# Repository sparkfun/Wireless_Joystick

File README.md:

SparkFun Wireless Joystick Kit
=============================================

[*SparkFun Wireless Joystick Kit (KIT-14051)*](https://www.sparkfun.com/products/14051)

What's in the kit:

* 1 - Wireless Joystick Board
* 2 - [Thumb Joysticks](https://www.sparkfun.com/products/9032)
* 2 - [Right Angle Momentary Push-Buttons](https://www.sparkfun.com/products/10791)
* 4 - [12mm Square Momentary Push Buttons](https://www.sparkfun.com/products/9190)

What's **not** in the kit:

* 1 - [Li-Ion battery](https://www.sparkfun.com/products/13851)
* 1 - [XBee](https://www.sparkfun.com/products/8665)

The SparkFun Wireless Joystick Kit is a customizable XBee wireless controller with a SAMD21 at the heart of the board. The controller can be configured in two ways; gamepad or dual-stick. The gamepad has a layout similar to the SNES gamepad, with a single joystick on the left and four push-buttons on the right, and two trigger buttons. The dual-stick configuration uses two analog joysticks, along with two trigger buttons. Dual joysticks are perfect for tank-steering robotics; the left joystick controls the motor(s) on the left side, and the right  joystick controls the motor(s) on the right side.
 
 Repository Contents
-------------------
* **/Hardware** - All Eagle design files (.brd, .sch)

Documentation
-------------------
* [**Hookup Guide**](https://learn.sparkfun.com/tutorials/wireless-joystick-hookup-guide)

License Information
-------------------
The hardware is released under [Creative Commons ShareAlike 4.0 International](https://creativecommons.org/licenses/by-sa/4.0/).
The code is beerware; if you see me (or any other SparkFun employee) at the local, and you've found our code helpful, please buy us a round!

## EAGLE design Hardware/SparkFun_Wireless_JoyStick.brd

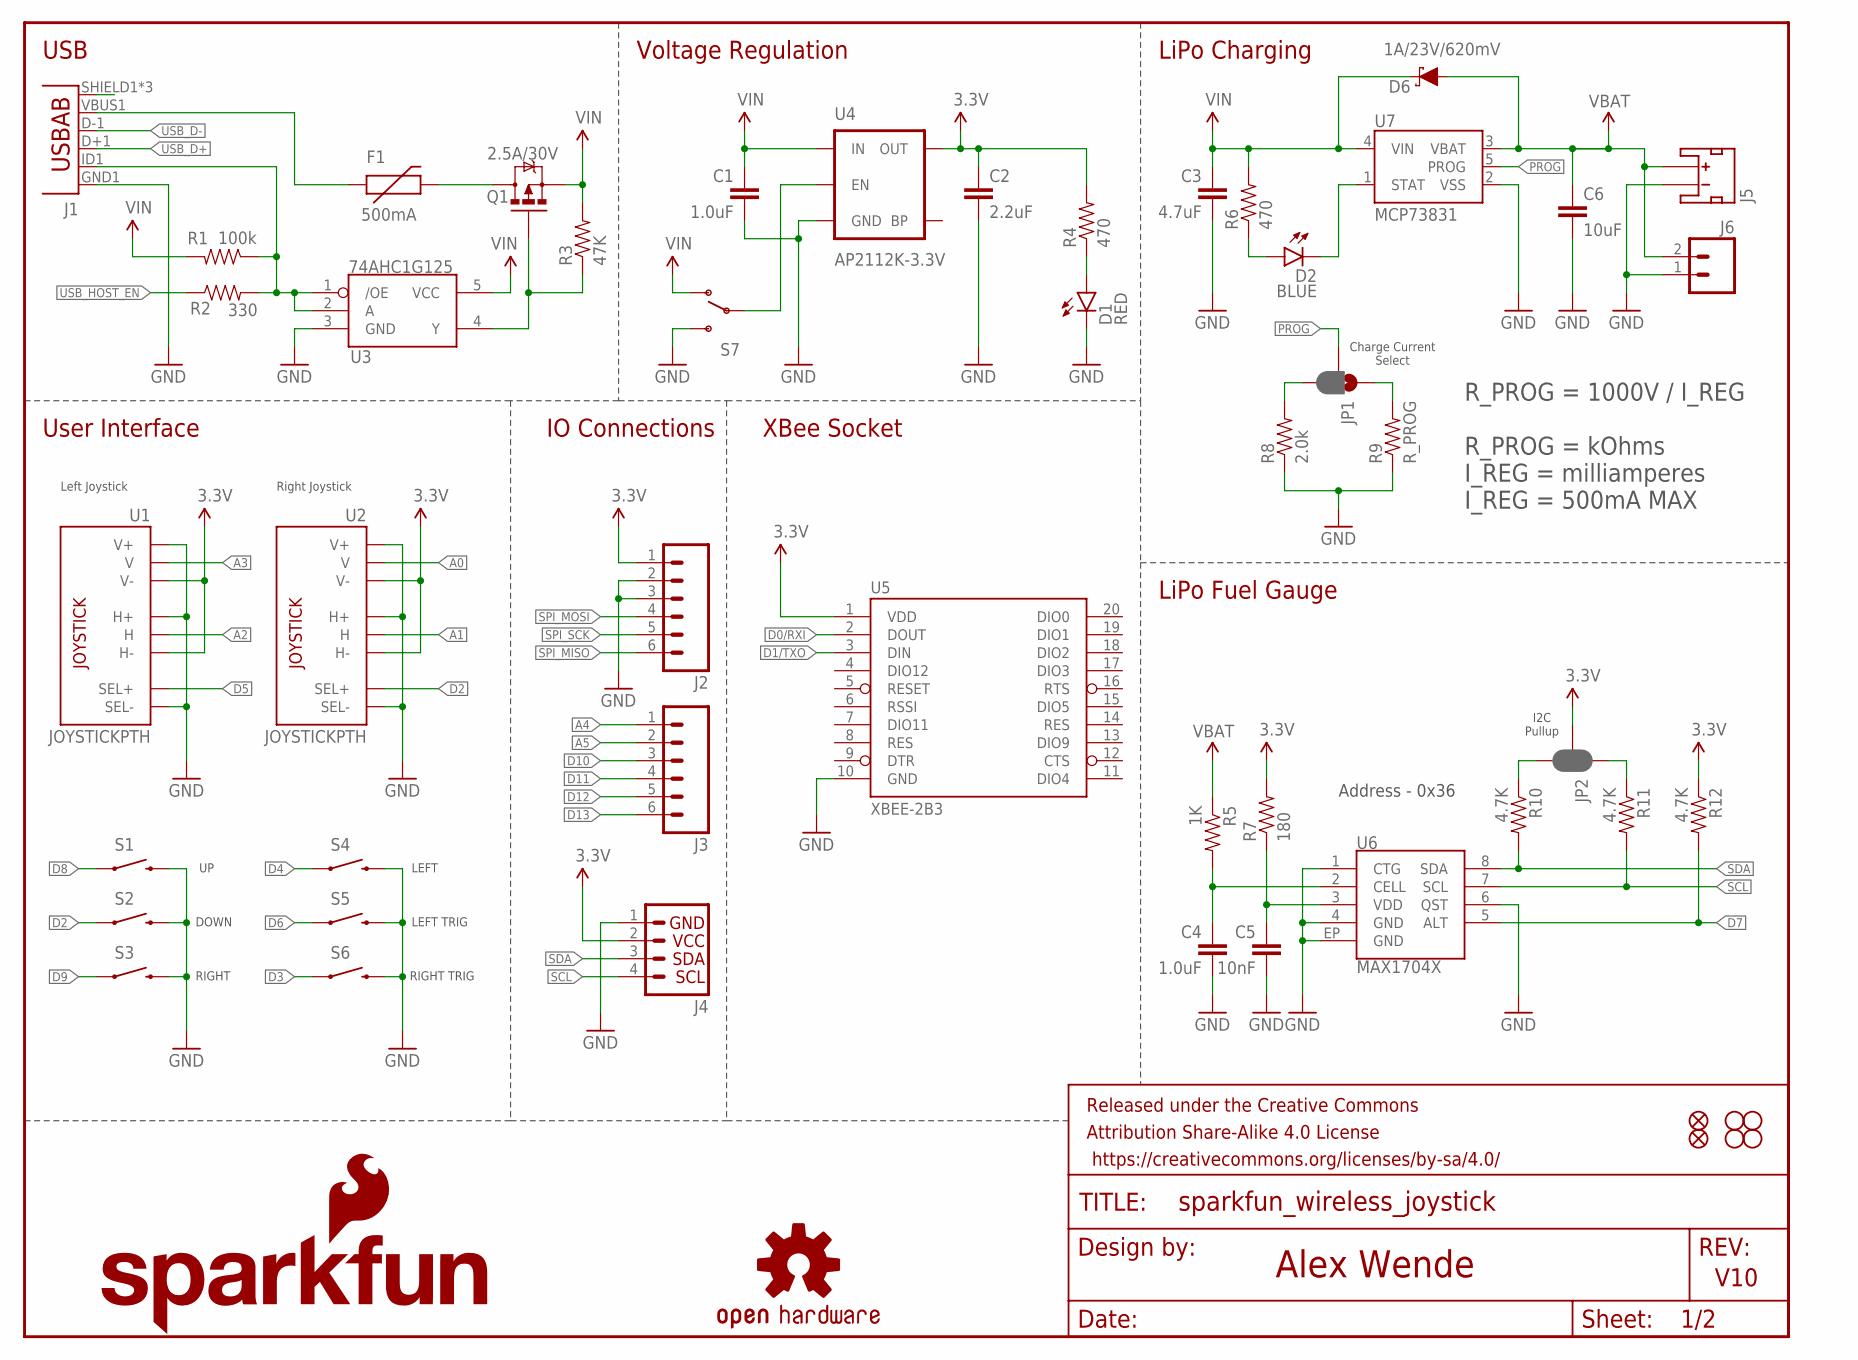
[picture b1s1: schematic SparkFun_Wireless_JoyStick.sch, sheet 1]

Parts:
C1: 1.0uF; 0805-CAP
C2: 2.2uF; 0603-CAP
C3: 4.7uF; 0603-CAP
C4: 1.0uF; 0603-CAP
C5: 10nF; 0603-CAP
C6: 10uF; 0603-CAP
D1: RED; LED-0603
D2: BLUE; LED-0603
D6: 1A/23V/620mV; SOD-323
F1: 500mA; PTC-1206
FD1, FD2: FIDUCIALUFIDUCIAL; MICRO-FIDUCIAL
FRAME1: FRAME-LETTER; CREATIVE_COMMONS
H1, H2, H3, H4: STAND-OFF
J1: USB-ABCONN-11794; USB-AB-MICRO-SMD_V03
J2, J3: M06NO_SILK_FEMALE_PTH; 1X06_NO_SILK
J4: I2C_STANDARD_NO_SILK; 1X04_NO_SILK
J5: JST_2MM_MALE; JST-2-SMD
J6: M021X02_NO_SILK; 1X02_NO_SILK
JP1: JUMPER-PAD-3-2OF3_NC_BY_PASTE; PAD-JUMPER-3-2OF3_NC_BY_PASTE_YES_SILK_FULL_BOX
JP2: JUMPER-PAD-3-NC_BY_PASTE; PAD-JUMPER-3-NC_BY_PASTE_YES_SILK_FULL_BOX
LOGO1: SFE_LOGO_NAME_FLAME.3_INCH; SFE_LOGO_NAME_FLAME_.3
LOGO2: OSHW-LOGOL; OSHW-LOGO-L
Q1: 2.5A/30V; SOT23-3@1
R1: 100k; 0603-RES
R2: 330; 0603-RES
R3: 47K; 0603-RES
R4, R6: 470; 0603-RES
R5: 1K; 0603-RES
R7: 180; 0603-RES
R8: 2.0k; 0603-RES
R9: R_PROG; AXIAL-0.4
R10, R11, R12: 4.7K; 0603-RES
S1, S2, S3, S4: SWITCH-MOMENTARY-212MM; TACTILE-PTH-12MM
S5, S6: SWITCH-MOMENTARY-2SIDE_EZ; TACTILE-PTH-SIDEEZ
S7: SWITCH_SPDT; KPS-1290
U1, U2: JOYSTICKPTH; JOYSTICK
U3: 74AHC1G125; SOT23-5
U4: AP2112K-3.3V; SOT23-5
U5: XBEE-2B3; XBEE-SMD
U6: MAX1704X; TDFN-8
U7: MCP73831; SOT23-5

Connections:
3.3V: C2.1, J2.1, J4.2, JP2.2, R4.2, R7.2, R12.1, U1.H3 (H-), U1.V3 (V-), U2.H3 (H-), U2.V3 (V-), U4.5 (OUT), U5.1 (VDD); also elsewhere on the board
A0: U2.V2 (V); also elsewhere on the board
A1: U2.H2 (H); also elsewhere on the board
A2: U1.H2 (H); also elsewhere on the board
A3: U1.V2 (V); also elsewhere on the board
A4: J3.1; also elsewhere on the board
A5: J3.2; also elsewhere on the board
D0/RXI: U5.2 (DOUT); also elsewhere on the board
D1/TXO: U5.3 (DIN); also elsewhere on the board
D2: S2.1, U2.B1A (SEL+); also elsewhere on the board
D3: S6.1; also elsewhere on the board
D4: S4.1; also elsewhere on the board
D5: U1.B1A (SEL+); also elsewhere on the board
D6: S5.1; also elsewhere on the board
D7: R12.2, U6.5 (ALT); also elsewhere on the board
D8: S1.1; also elsewhere on the board
D9: S3.1; also elsewhere on the board
D10: J3.3; also elsewhere on the board
D11: J3.4; also elsewhere on the board
D12: J3.5; also elsewhere on the board
D13: J3.6; also elsewhere on the board
GND: C1.2, C2.2, C3.2, C4.2, C5.2, C6.2, D1.C, J1.GND1 (GND), J2.2, J2.3, J4.1, J5.1 (-), J6.1, R8.1, R9.P$1 (1), S1.3 (2), S2.3 (2), S3.3 (2), S4.3 (2), S5.2, S6.2, S7.S, U1.B2A (SEL-), U1.H1 (H+), U1.V1 (V+), U2.B2A (SEL-), U2.H1 (H+), U2.V1 (V+), U3.3 (GND), U4.2 (GND), U5.10 (GND), U6.1 (CTG), U6.4 (GND), U6.6 (QST), U6.EP (GND), U7.2 (VSS); also elsewhere on the board
unnamed: JP2.1, R11.1
unnamed: JP2.3, R10.1
unnamed: JP1.1, R9.P$2 (2)
unnamed: F1.1, J1.VBUS1 (VBUS)
unnamed: C5.1, R7.1, U6.3 (VDD)
unnamed: S7.P, U4.3 (EN)
unnamed: F1.2, Q1.3 (D)
unnamed: J1.ID1 (USBID), R1.1, R2.2, U3.1 (/OE), U3.2 (A)
unnamed: C4.1, R5.2, U6.2 (CELL)
unnamed: JP1.3, R8.2
unnamed: D2.A, R6.1
unnamed: D2.C, U7.1 (STAT)
unnamed: D1.A, R4.1
unnamed: Q1.1 (G), R3.1, U3.4 (Y)
PROG: JP1.2, U7.5 (PROG)
SCL: J4.4, R11.2, U6.7 (SCL); also elsewhere on the board
SDA: J4.3, R10.2, U6.8 (SDA); also elsewhere on the board
SHIELD: J1.SHIELD1 (SHIELD), J1.SHIELD2 (SHIELD), J1.SHIELD3 (SHIELD)
SPI_MISO: J2.6; also elsewhere on the board
SPI_MOSI: J2.4; also elsewhere on the board
SPI_SCK: J2.5; also elsewhere on the board
USB_D+: J1.D+1 (D+); also elsewhere on the board
USB_D-: J1.D-1 (D-); also elsewhere on the board
USB_HOST_EN: R2.1; also elsewhere on the board
VBAT: C6.1, D6.A, J5.2 (+), J6.2, R5.1, U7.3 (VBAT)
VIN: C1.1, C3.1, D6.C, Q1.2 (S), R1.2, R3.2, R6.2, S7.O, U3.5 (VCC), U4.1 (IN), U7.4 (VIN)

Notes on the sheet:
User Interface
USB
LiPo Charging
Voltage Regulation
XBee Socket
R_PROG = 1000V / I_REG
R_PROG = kOhms I_REG = milliamperes I_REG = 500mA MAX
LiPo Fuel Gauge
Alex Wende
V10
Right Joystick
Left Joystick
DOWN
RIGHT
LEFT
LEFT TRIG
RIGHT TRIG
IO Connections
I2C Pullup
Charge Current Select
Address - 0x36

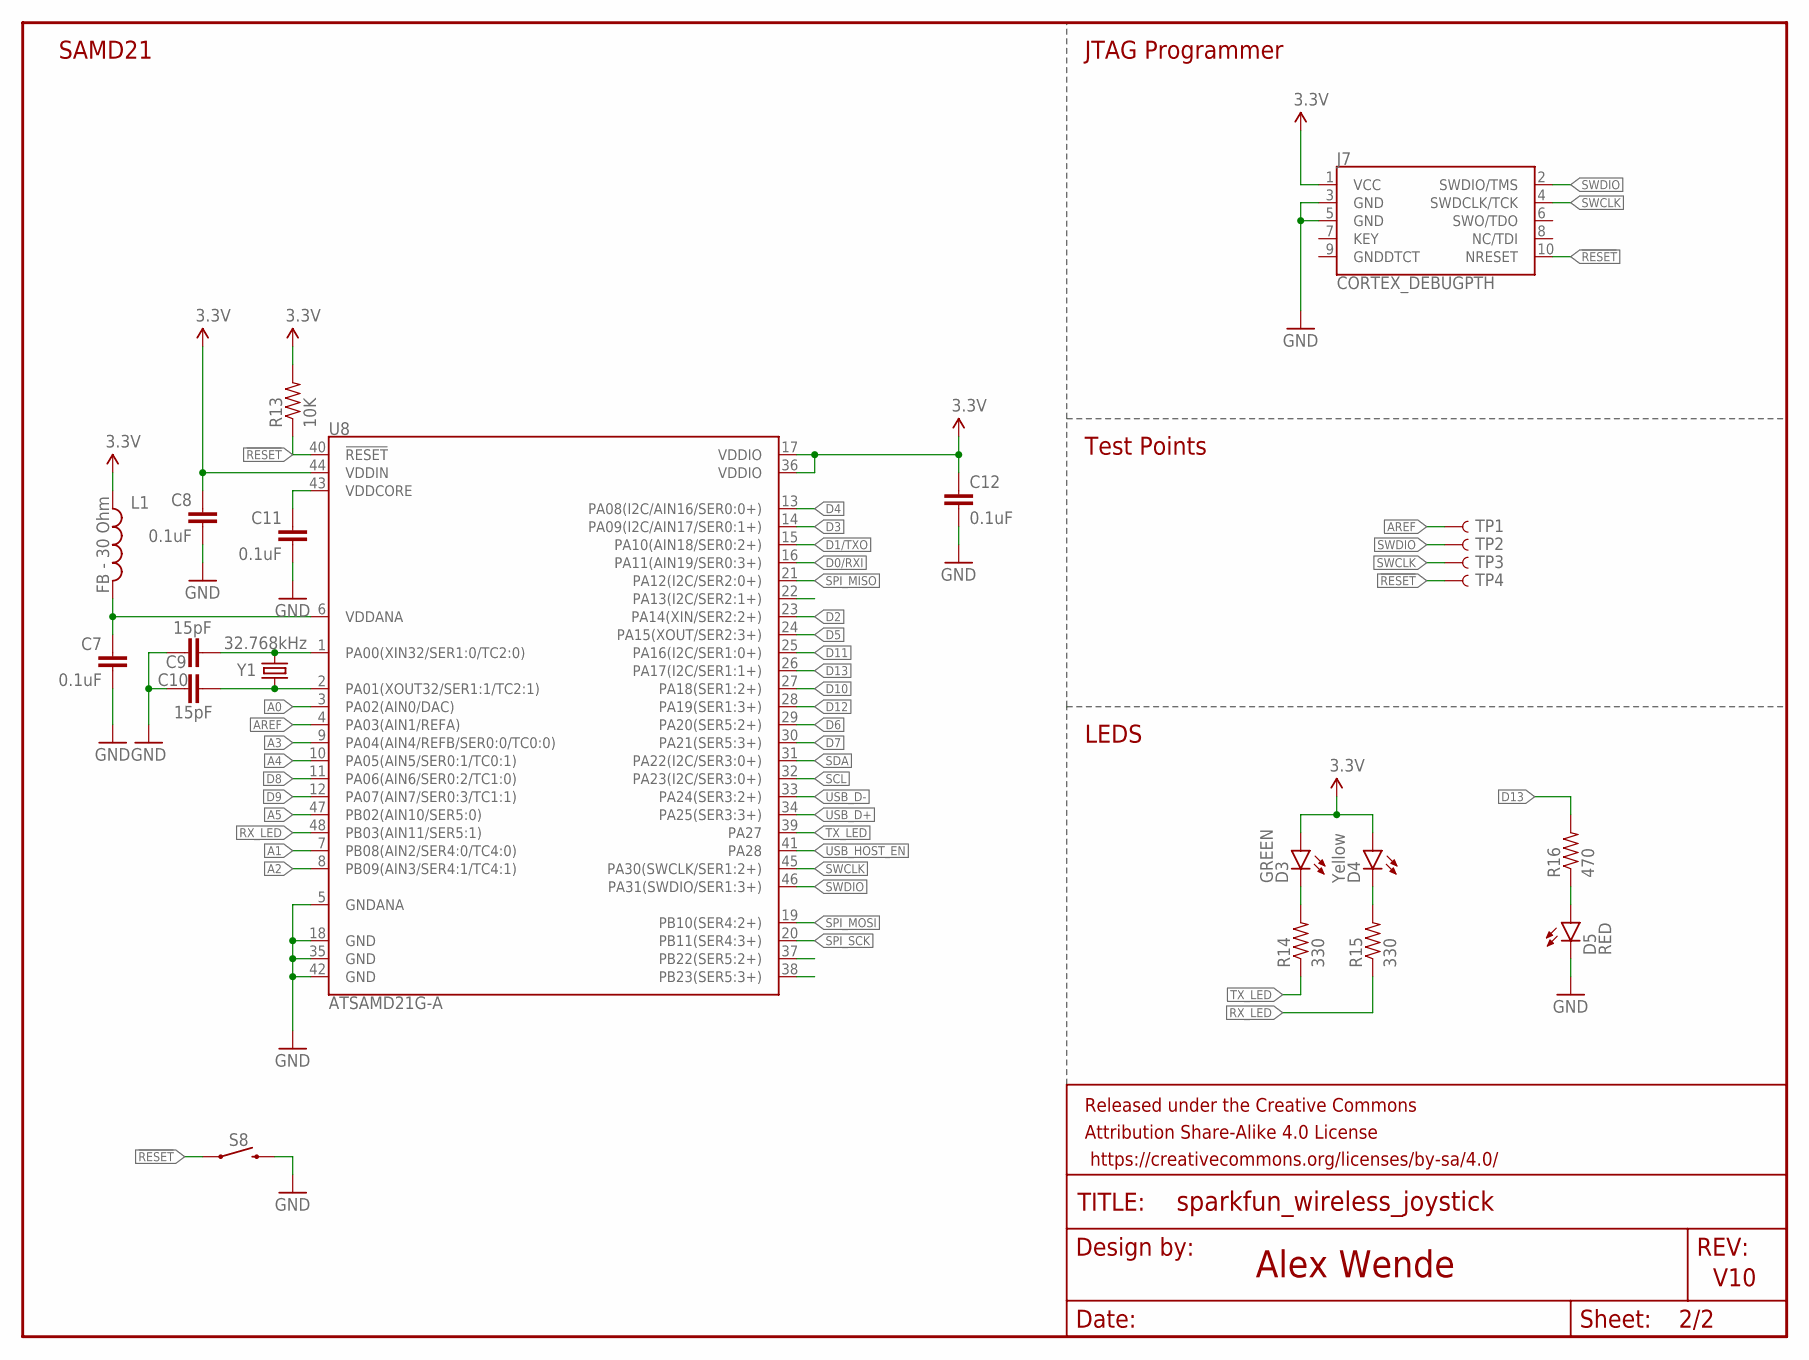
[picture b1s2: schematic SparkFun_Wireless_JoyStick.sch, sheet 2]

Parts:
C7, C8, C11, C12: 0.1uF; 0603-CAP
C9, C10: 15pF; 0603-CAP
D3: GREEN; LED-0603
D4: Yellow; LED-0603
D5: RED; LED-0603
FRAME2: FRAME-LETTERNO_PACKAGE; DUMMY
J7: CORTEX_DEBUGPTH; 2X5-PTH-1.27MM
L1: FB - 30 Ohm; 0603
R13: 10K; 0603-RES
R14, R15: 330; 0603-RES
R16: 470; 0603-RES
S8: MOMENTARY-SWITCH-SPST-SMD-4.6X2.8MM; TACTILE_SWITCH_SMD_4.6X2.8MM
TP1, TP2, TP3, TP4: TEST-POINT3; PAD.03X.03
U8: ATSAMD21G-A; TQFP-48
Y1: 32.768kHz; CRYSTAL-SMD-3.2X1.5MM

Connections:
3.3V: C8.1, C12.1, D3.A, D4.A, J7.1 (VCC), L1.1, R13.2, U8.17 (VDDIO), U8.36 (VDDIO), U8.44 (VDDIN); also elsewhere on the board
!RESET: J7.10 (NRESET), R13.1, S8.1, S8.2 (1), TP4.P$1, U8.40 (!RESET!)
A0: U8.3 (PA02(AIN0/DAC)); also elsewhere on the board
A1: U8.7 (PB08(AIN2/SER4:0/TC4:0)); also elsewhere on the board
A2: U8.8 (PB09(AIN3/SER4:1/TC4:1)); also elsewhere on the board
A3: U8.9 (PA04(AIN4/REFB/SER0:0/TC0:0)); also elsewhere on the board
A4: U8.10 (PA05(AIN5/SER0:1/TC0:1)); also elsewhere on the board
A5: U8.47 (PB02(AIN10/SER5:0)); also elsewhere on the board
AREF: TP1.P$1, U8.4 (PA03(AIN1/REFA))
D0/RXI: U8.16 (PA11(AIN19/SER0:3+)); also elsewhere on the board
D1/TXO: U8.15 (PA10(AIN18/SER0:2+)); also elsewhere on the board
D2: U8.23 (PA14(XIN/SER2:2+)); also elsewhere on the board
D3: U8.14 (PA09(I2C/AIN17/SER0:1+)); also elsewhere on the board
D4: U8.13 (PA08(I2C/AIN16/SER0:0+)); also elsewhere on the board
D5: U8.24 (PA15(XOUT/SER2:3+)); also elsewhere on the board
D6: U8.29 (PA20(SER5:2+)); also elsewhere on the board
D7: U8.30 (PA21(SER5:3+)); also elsewhere on the board
D8: U8.11 (PA06(AIN6/SER0:2/TC1:0)); also elsewhere on the board
D9: U8.12 (PA07(AIN7/SER0:3/TC1:1)); also elsewhere on the board
D10: U8.27 (PA18(SER1:2+)); also elsewhere on the board
D11: U8.25 (PA16(I2C/SER1:0+)); also elsewhere on the board
D12: U8.28 (PA19(SER1:3+)); also elsewhere on the board
D13: R16.2, U8.26 (PA17(I2C/SER1:1+)); also elsewhere on the board
GND: C7.2, C8.2, C9.1, C10.1, C11.2, C12.2, D5.C, J7.3 (GND), J7.5 (GND), S8.3 (2), S8.4 (2), U8.5 (GNDANA), U8.18 (GND), U8.35 (GND), U8.42 (GND); also elsewhere on the board
unnamed: D4.C, R15.2
unnamed: D5.A, R16.1
unnamed: D3.C, R14.2
unnamed: C11.1, U8.43 (VDDCORE)
unnamed: C9.2, U8.1 (PA00(XIN32/SER1:0/TC2:0)), Y1.P$2 (2)
unnamed: C10.2, U8.2 (PA01(XOUT32/SER1:1/TC2:1)), Y1.P$1 (1)
unnamed: C7.1, L1.2, U8.6 (VDDANA)
RX_LED: R15.1, U8.48 (PB03(AIN11/SER5:1))
SCL: U8.32 (PA23(I2C/SER3:0+)); also elsewhere on the board
SDA: U8.31 (PA22(I2C/SER3:0+)); also elsewhere on the board
SPI_MISO: U8.21 (PA12(I2C/SER2:0+)); also elsewhere on the board
SPI_MOSI: U8.19 (PB10(SER4:2+)); also elsewhere on the board
SPI_SCK: U8.20 (PB11(SER4:3+)); also elsewhere on the board
SWCLK: J7.4 (SWDCLK/TCK), TP3.P$1, U8.45 (PA30(SWCLK/SER1:2+))
SWDIO: J7.2 (SWDIO/TMS), TP2.P$1, U8.46 (PA31(SWDIO/SER1:3+))
TX_LED: R14.1, U8.39 (PA27)
USB_D+: U8.34 (PA25(SER3:3+)); also elsewhere on the board
USB_D-: U8.33 (PA24(SER3:2+)); also elsewhere on the board
USB_HOST_EN: U8.41 (PA28); also elsewhere on the board

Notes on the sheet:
Alex Wende
V10
SAMD21
JTAG Programmer
Test Points
LEDS

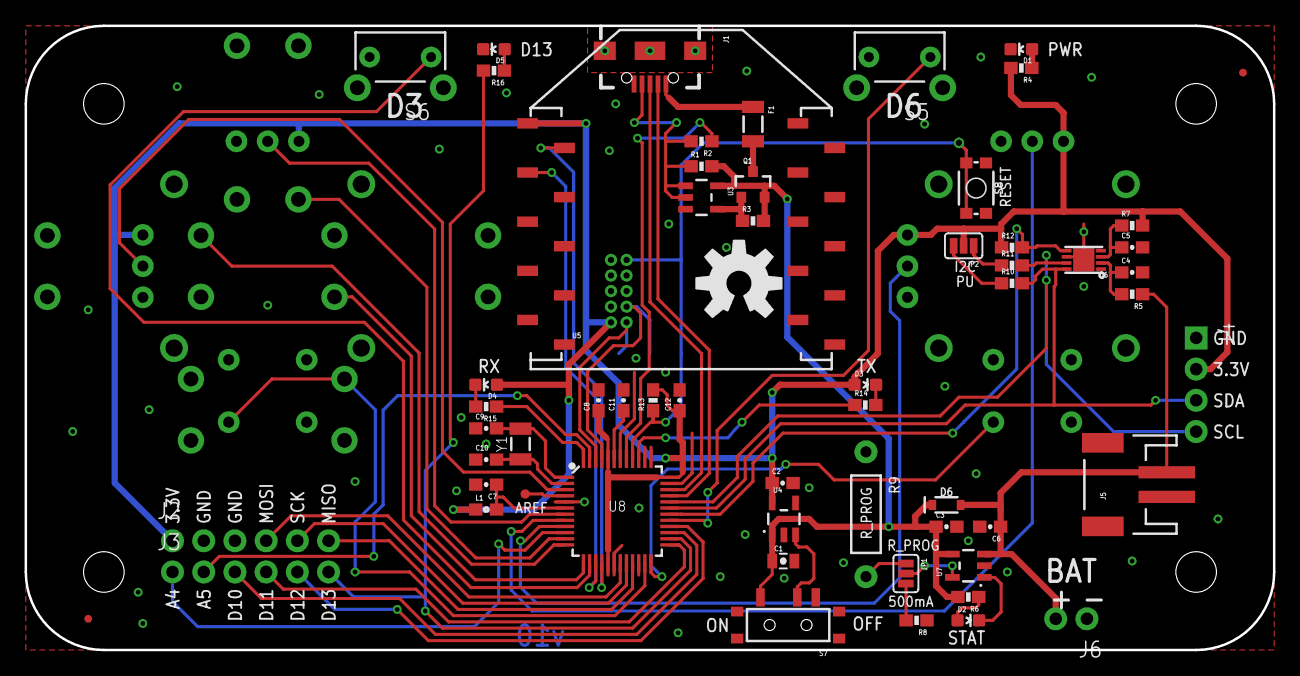
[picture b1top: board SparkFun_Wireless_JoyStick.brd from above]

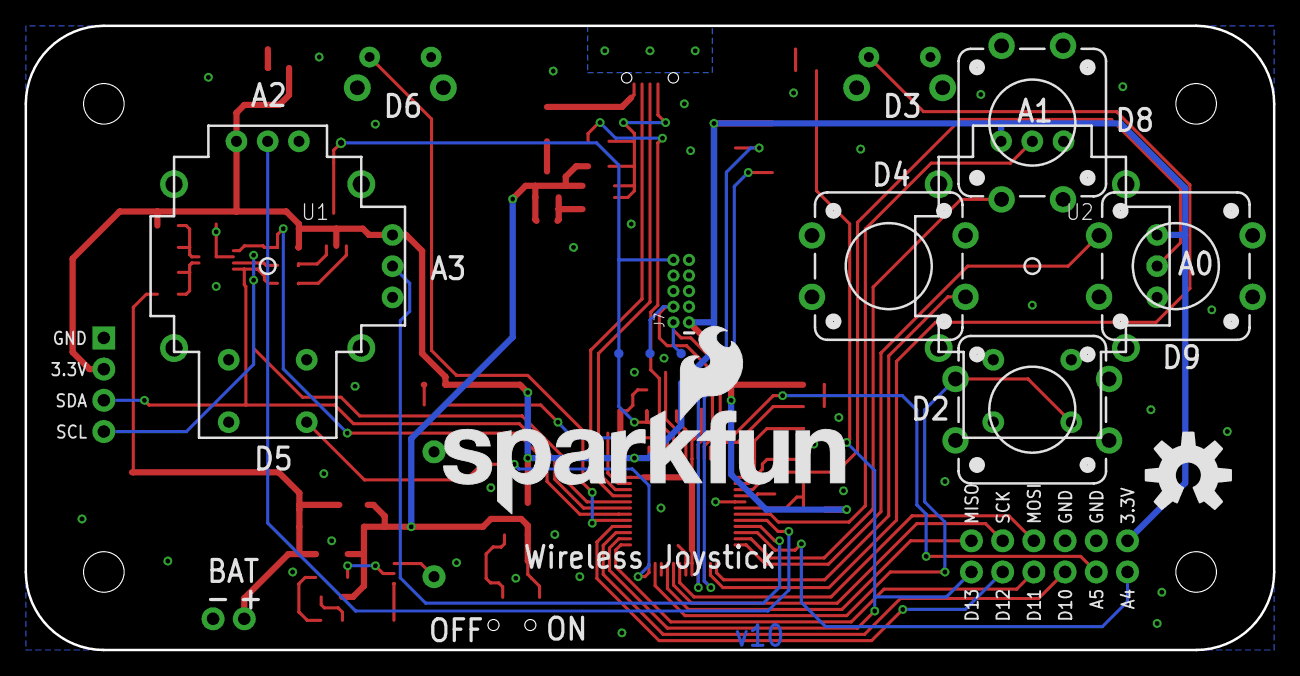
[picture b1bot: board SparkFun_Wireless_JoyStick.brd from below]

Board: 2 copper layers, 101.6 x 50.8 mm, 78 parts (12 on the bottom side), 61 nets.

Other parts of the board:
LOGO3: OSHW-LOGOL; OSHW-LOGO-L

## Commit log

2016-08-08 Initial Commit
    Adding Eagle files
2016-08-09 V10 Updates
    - Broke out extra pins
    - Added LiPo fuel gauge
    - Added "trigger" buttons
    - Cleaned up layout
2016-08-11 V10 update
    - Broke out a few more pins
    - Cleaned up the schematic
2016-08-15 V10 Updates
2016-08-16 Design Review Changes
    - Added LED to D13 for low batt indication.
    - Added test points for bootloader programming from testbed
2016-08-16 Minor Changes
    Too minor to mention
2016-08-19 QC Issues Fixed
    - TX_LED and RX_LED nets are now all 0.006" width
    - Version number changed to v01
    - IO connections use 3.3V and GND symbols instead of net labels
    - Replaced VBAT net label in LiPo Fuel Gauge with PWR symbol
    - Inductor PROD_ID updated to match SKU in Sparkle
    - Moved JTAG test points to bottom copper
2016-09-22 Proto Changes
    - Added diode to allow powering the board from USB when no battery is
    present.
    - Switch now controls enable pin instead of VCC rail
2016-09-22 Updating version to 10
2016-09-22 Updating to version 10
2016-09-23 Added fuel gauge i2c address
2016-09-26 Minor Changes
    - added reset switch
    - reversed power and ground on joysticks
2016-09-26 Moved gnd via
    Moved ground via that was too close to a trace

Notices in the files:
parts and their libraries:
SparkFun-Capacitors: Licensing: Creative Commons ShareAlike 4.0 International - https://creativecommons.org/licenses/by-sa/4.0
SparkFun-Aesthetics: Released under the Creative Commons Attribution Share-Alike 4.0 License
SparkFun-Aesthetics: Released under the Creative Commons
